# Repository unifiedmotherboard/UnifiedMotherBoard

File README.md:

# The Unified Mother Board project aims to create a standard for small form-factor keyboard microcontrollers.
## Goals:
- Simplify process for keyboard designers by offloading MCU design to UMB
- Provide a smaller form factor than other external microcontroller options (i.e. ProMicro)
- Allow the same keyboard "shield" to support many different microcontrollers depending on firmware or power requirements
- Reduction of e-waste by providing a verified MCU base

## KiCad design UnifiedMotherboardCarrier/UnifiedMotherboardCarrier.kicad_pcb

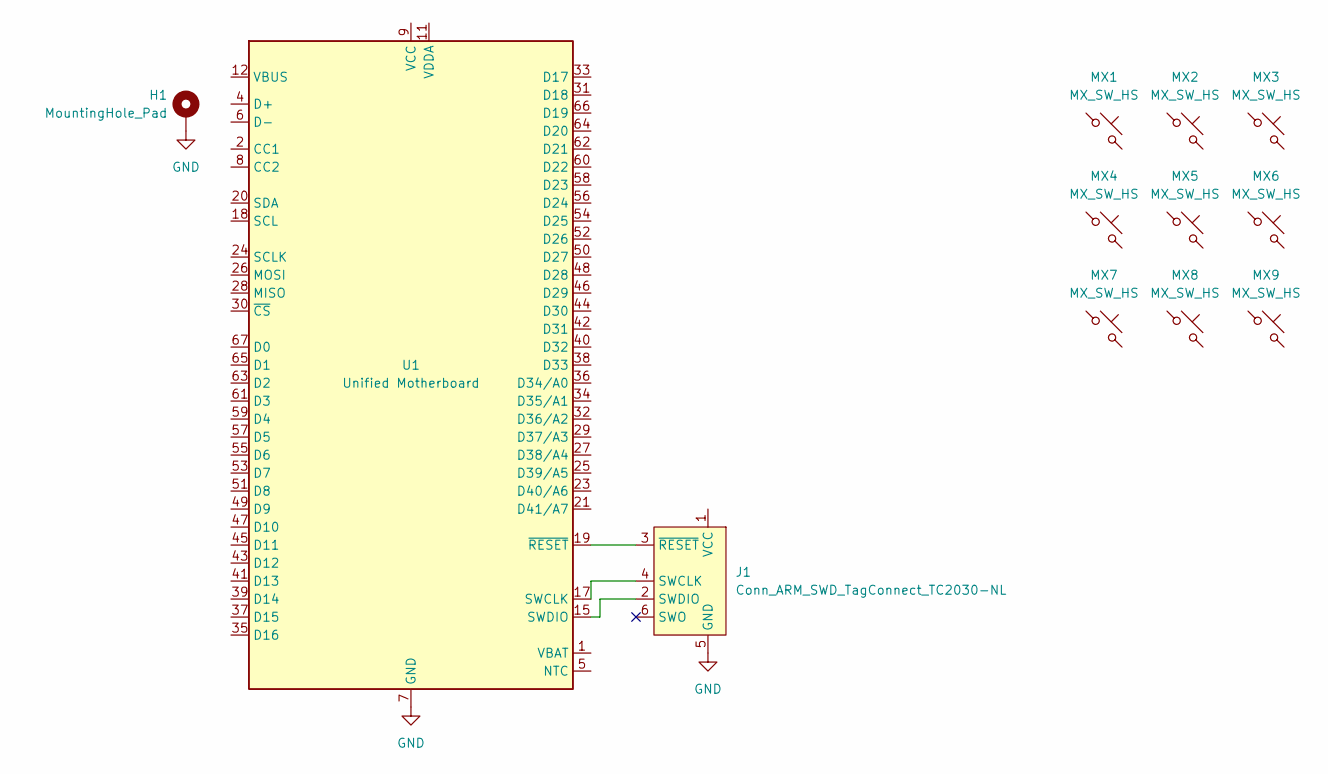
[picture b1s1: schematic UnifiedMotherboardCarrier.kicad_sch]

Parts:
H1: MountingHole_Pad; SMTSO3025CTJ; LCSC C2916365
J1: Conn_ARM_SWD_TagConnect_TC2030-NL; Tag-Connect_TC2030-IDC-NL_2x03_P1.27mm_Vertical
MX1, MX2, MX3, MX4, MX5, MX6, MX7, MX8, MX9: MX_SW_HS; SW_MX_HS_CPG151101S11_1u
U1: Unified Motherboard; TEConnectivity-1-2199230-6-67-P0.5mm; LCSC C2977809

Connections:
GND: H1.1, J1.5 (GND), U1.7 (GND), U1.10 (GND), U1.13 (GND), U1.16 (GND), U1.22 (GND), U1.MP
unnamed: J1.4 (SWCLK), U1.17 (SWCLK)
unnamed: J1.2 (SWDIO), U1.15 (SWDIO)
unnamed: J1.3 (~RESET), U1.19 (~RESET)
unnamed: U1.1 (VBAT), U1.3 (VBAT)
unnamed: U1.12 (VBUS), U1.14 (VBUS)

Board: 2 copper layers, 12 parts (11 on the bottom side), 6 nets, no tracks yet.

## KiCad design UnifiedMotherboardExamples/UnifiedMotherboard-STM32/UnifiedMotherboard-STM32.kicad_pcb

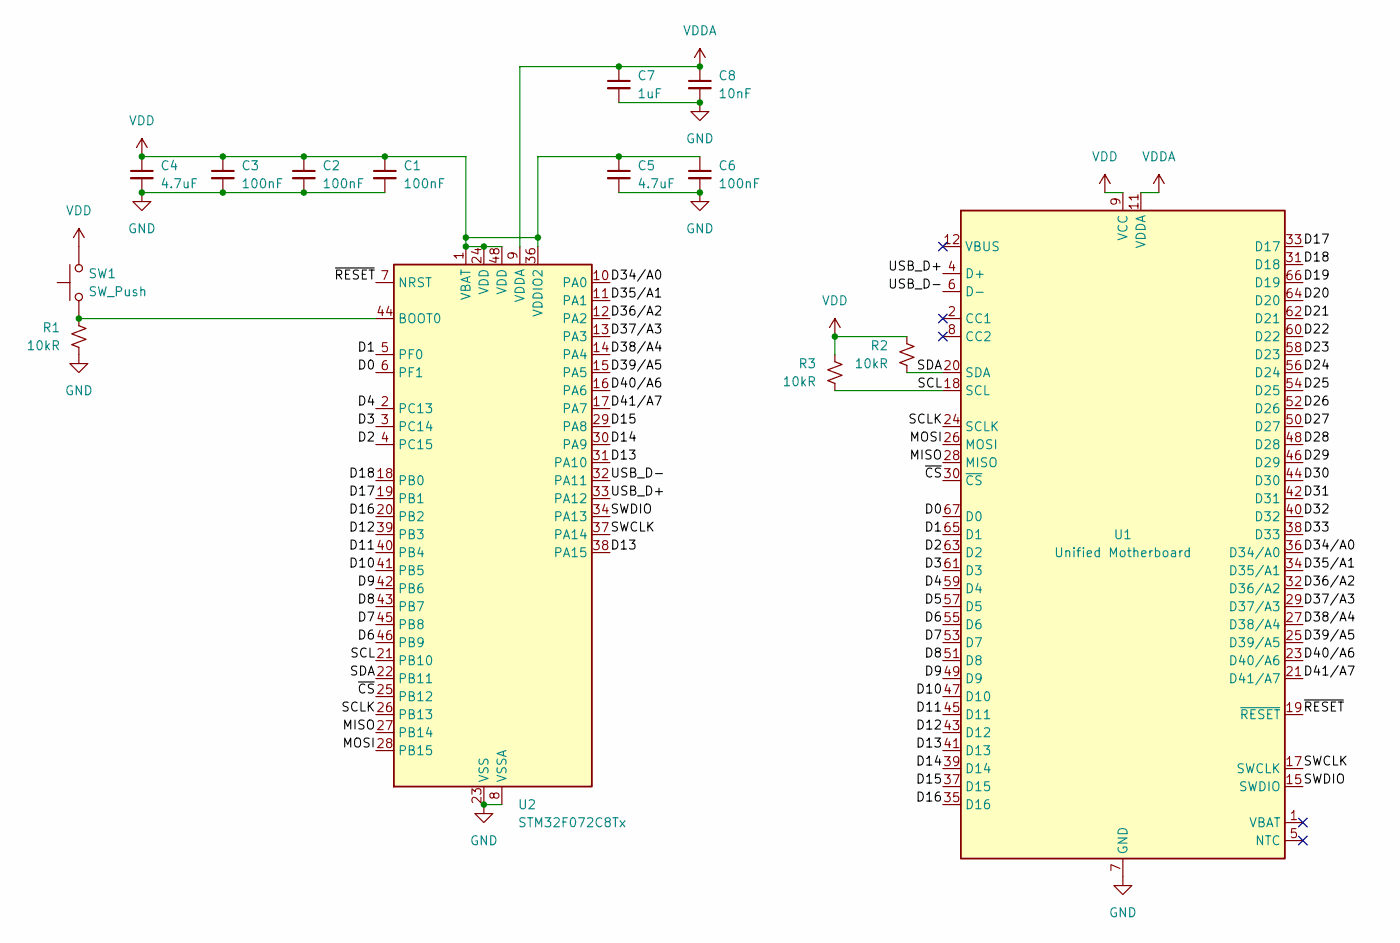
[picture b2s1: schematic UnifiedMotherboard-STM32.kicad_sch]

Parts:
C1, C2, C3, C6: 100nF; C_0402_1005Metric; LCSC C1525
C4, C5: 4.7uF; C_0805_2012Metric; LCSC C1779
C7: 1uF; C_0402_1005Metric; LCSC C52923
C8: 10nF; C_0402_1005Metric; LCSC C15195
R1, R2, R3: 10kR; R_0402_1005Metric; LCSC C25744
SW1: SW_Push; SW_Push_1P1T_NO_Vertical_Wuerth_434133025816; LCSC C139797
U1: Unified Motherboard; UnifiedMotherboard
U2: STM32F072C8Tx; LQFP-48_7x7mm_P0.5mm; LCSC C80488

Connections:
/D0: U1.67 (D0), U2.6 (PF1)
/D1: U1.65 (D1), U2.5 (PF0)
/D2: U1.63 (D2), U2.4 (PC15)
/D3: U1.61 (D3), U2.3 (PC14)
/D4: U1.59 (D4), U2.2 (PC13)
/D5: U1.57 (D5)
/D6: U1.55 (D6), U2.46 (PB9)
/D7: U1.53 (D7), U2.45 (PB8)
/D8: U1.51 (D8), U2.43 (PB7)
/D9: U1.49 (D9), U2.42 (PB6)
/D10: U1.47 (D10), U2.41 (PB5)
/D11: U1.45 (D11), U2.40 (PB4)
/D12: U1.43 (D12), U2.39 (PB3)
/D13: U1.41 (D13), U2.31 (PA10), U2.38 (PA15)
/D14: U1.39 (D14), U2.30 (PA9)
/D15: U1.37 (D15), U2.29 (PA8)
/D16: U1.35 (D16), U2.20 (PB2)
/D17: U1.33 (D17), U2.19 (PB1)
/D18: U1.31 (D18), U2.18 (PB0)
/D19: U1.66 (D19)
/D20: U1.64 (D20)
/D21: U1.62 (D21)
/D22: U1.60 (D22)
/D23: U1.58 (D23)
/D24: U1.56 (D24)
/D25: U1.54 (D25)
/D26: U1.52 (D26)
/D27: U1.50 (D27)
/D28: U1.48 (D28)
/D29: U1.46 (D29)
/D30: U1.44 (D30)
/D31: U1.42 (D31)
/D32: U1.40 (D32)
/D33: U1.38 (D33)
/D34/A0: U1.36 (D34/A0), U2.10 (PA0)
/D35/A1: U1.34 (D35/A1), U2.11 (PA1)
/D36/A2: U1.32 (D36/A2), U2.12 (PA2)
/D37/A3: U1.29 (D37/A3), U2.13 (PA3)
/D38/A4: U1.27 (D38/A4), U2.14 (PA4)
/D39/A5: U1.25 (D39/A5), U2.15 (PA5)
/D40/A6: U1.23 (D40/A6), U2.16 (PA6)
/D41/A7: U1.21 (D41/A7), U2.17 (PA7)
/MISO: U1.28 (MISO), U2.27 (PB14)
/MOSI: U1.26 (MOSI), U2.28 (PB15)
/SCL: R3.2, U1.18 (SCL), U2.21 (PB10)
/SCLK: U1.24 (SCLK), U2.26 (PB13)
/SDA: R2.2, U1.20 (SDA), U2.22 (PB11)
/SWCLK: U1.17 (SWCLK), U2.37 (PA14)
/SWDIO: U1.15 (SWDIO), U2.34 (PA13)
/USB_D+: U1.4 (D+), U2.33 (PA12)
/USB_D-: U1.6 (D-), U2.32 (PA11)
/~CS: U1.30 (~CS), U2.25 (PB12)
/~RESET: U1.19 (~RESET), U2.7 (NRST)
GND: C1.2, C2.2, C3.2, C4.2, C5.2, C6.2, C7.2, C8.2, R1.2, U1.7 (GND), U1.10 (GND), U1.13 (GND), U1.16 (GND), U1.22 (GND), U1.MP, U2.8 (VSSA), U2.23 (VSS), U2.35 (VSS), U2.47 (VSS)
unnamed: R1.1, SW1.1, U2.44 (BOOT0)
VDD: C1.1, C2.1, C3.1, C4.1, C5.1, C6.1, R2.1, R3.1, SW1.2, U1.9 (VCC), U2.1 (VBAT), U2.24 (VDD), U2.36 (VDDIO2), U2.48 (VDD)
VDDA: C7.1, C8.1, U1.11 (VDDA), U2.9 (VDDA)

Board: 4 copper layers, 14 parts (0 on the bottom side), 41 nets, no tracks yet.

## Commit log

2024-05-01 Initial data commit for schematic WIP
2024-05-01 docs: readme
    Initial draft of README. Would like comments. Will also
    update with pictures of basic template
    once we're there.
2024-05-02 docs: pin assignment
    Added table for pin assignments
2024-05-02 template: meta
    Created basic template info.
2024-05-02 Updated KiCAD files to V8
2024-06-02 Added: Pin Assignment and Distribution Chart.
    Added Pin Assignment and Distribution Chart in XLSX and PDF format for improved developer understanding of pinout and distribution according to requirements
2024-06-02 Add Pin Configuration and Abstraction Char
    Added Pin Configuration and Abstraction Chart in XLSX and PDF format for developer understanding. Includes priority, fixed, vendor, and GPIO pin information, providing a high-level overview of the sy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
2024-06-18 Added Unified Mother board Socket
2024-06-18 Updated schematic and pcb layout
2024-11-10 Updated LICENSE to CERN OHLv2
2024-11-10 Updated library with UMB symbols and footprints
2024-11-10 Removed old pin definition documentation
2024-11-10 Restructured example directories
2024-11-10 Update symbol and footprint to include keepout, SWD pins
2024-11-10 Schematic for STM32F072 design
2024-11-10 Added standoff footprint
2024-11-10 Started carrier board
